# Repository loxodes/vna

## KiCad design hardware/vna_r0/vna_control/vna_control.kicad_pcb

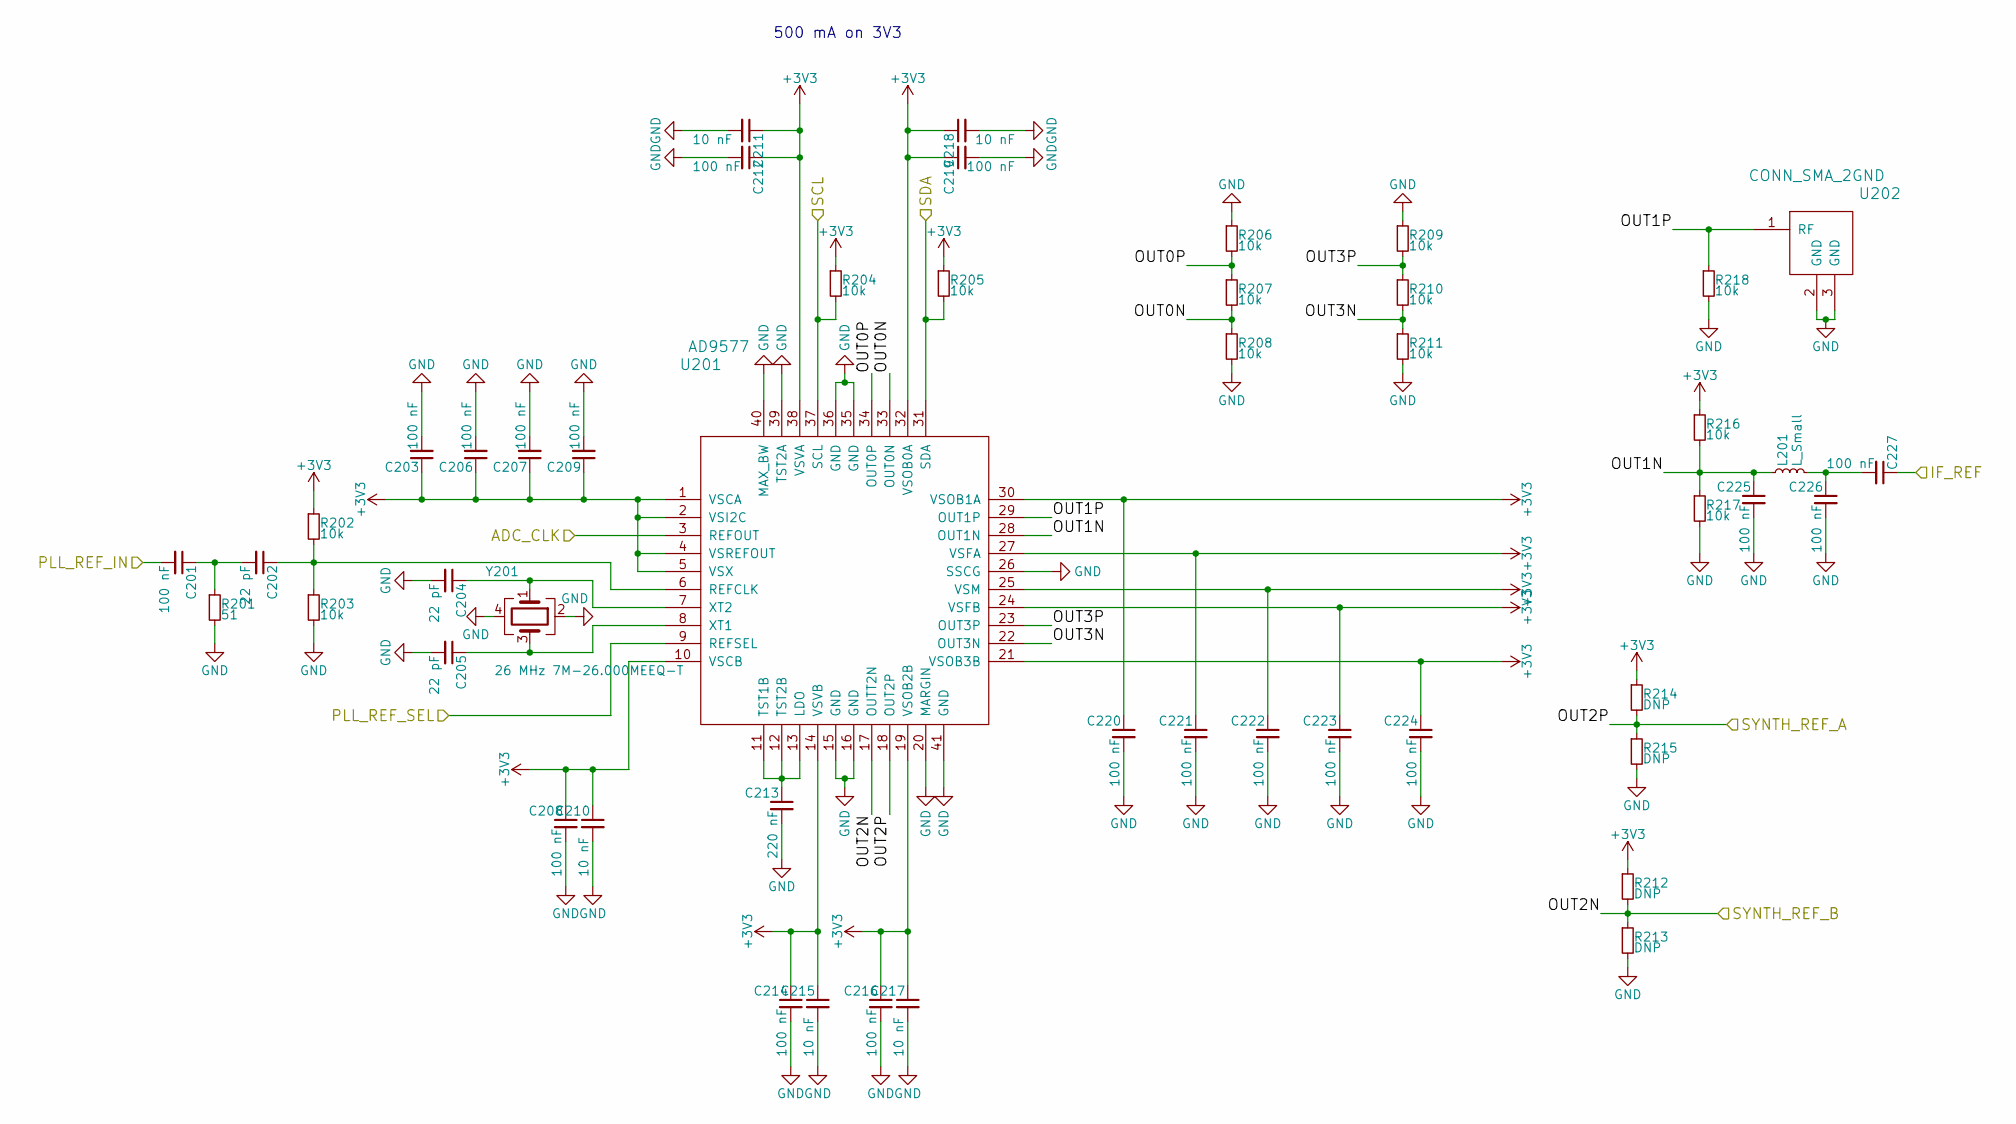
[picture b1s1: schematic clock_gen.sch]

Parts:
C201, C203, C206, C207, C208, C209, C212, C214, C216, C219, C220, C221, C222, C223, C224, C225, C226, C227: 100 nF; C_0402
C202, C204, C205: 22 pF; C_0402
C210, C211, C215, C217, C218: 10 nF; C_0402
C213: 220 nF; C_0402
L201: L_Small; R_0805
R201: 51; R_0402
R202, R203, R204, R205, R206, R207, R208, R209, R210, R211, R216, R217, R218: 10k; R_0402
R212, R213, R214, R215: DNP; R_0402
U201: AD9577; QFN-40-1EP_6x6mm_Pitch0.5mm
U202: CONN_SMA_2GND; 734120110_ufl_umc
Y201: 26 MHz 7M-26.000MEEQ-T; crystal_FA238-TSX3225

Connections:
+3V3: C203.1, C206.1, C207.1, C208.1, C209.1, C210.1, C211.1, C212.1, C214.1, C215.1, C216.1, C217.1, C218.1, C219.1, C220.1, C221.1, C222.1, C223.1, C224.1, R202.1, R204.1, R205.1, R212.1, R214.1, R216.1, U201.1 (VSCA), U201.2 (VSI2C), U201.4 (VSREFOUT), U201.5 (VSX), U201.10 (VSCB), U201.14 (VSVB), U201.19 (VSOB2B), U201.21 (VSOB3B), U201.24 (VSFB), U201.25 (VSM), U201.27 (VSFA), U201.30 (VSOB1A), U201.32 (VSOB0A), U201.38 (VSVA); also elsewhere on the board
/PLL_REF_SEL: U201.9 (REFSEL); also elsewhere on the board
/SCL: R204.2, U201.37 (SCL); also elsewhere on the board
/SDA: R205.2, U201.31 (SDA); also elsewhere on the board
/clock_gen/ADC_CLK: U201.3 (REFOUT); also elsewhere on the board
/clock_gen/IF_REF: C227.1; also elsewhere on the board
/clock_gen/OUT0N: R207.2, R208.1, U201.33 (OUT0N)
/clock_gen/OUT0P: R206.2, R207.1, U201.34 (OUT0P)
/clock_gen/OUT1N: C225.1, L201.1, R216.2, R217.1, U201.28 (OUT1N)
/clock_gen/OUT1P: R218.1, U201.29 (OUT1P), U202.1 (RF)
/clock_gen/OUT3N: R210.2, R211.1, U201.22 (OUT3N)
/clock_gen/OUT3P: R209.2, R210.1, U201.23 (OUT3P)
/clock_gen/PLL_REF_IN: C201.2; also elsewhere on the board
/clock_gen/SYNTH_REF_A: R214.2, R215.1, U201.18 (OUT2P); also elsewhere on the board
/clock_gen/SYNTH_REF_B: R212.2, R213.1, U201.17 (OUTT2N); also elsewhere on the board
GND: C203.2, C204.2, C205.2, C206.2, C207.2, C208.2, C209.2, C210.2, C211.2, C212.2, C213.2, C214.2, C215.2, C216.2, C217.2, C218.2, C219.2, C220.2, C221.2, C222.2, C223.2, C224.2, C225.2, C226.2, R201.2, R203.2, R206.1, R208.2, R209.1, R211.2, R213.2, R215.2, R217.2, R218.2, U201.15 (GND), U201.16 (GND), U201.20 (MARGIN), U201.26 (SSCG), U201.35 (GND), U201.36 (GND), U201.39 (TST2A), U201.40 (MAX_BW), U201.41 (GND), U202.2 (GND), U202.3 (GND), Y201.2, Y201.4; also elsewhere on the board
unnamed: C201.1, C202.2, R201.1
unnamed: C202.1, R202.2, R203.1, U201.6 (REFCLK)
unnamed: C204.1, U201.7 (XT2), Y201.1
unnamed: C205.1, U201.8 (XT1), Y201.3
unnamed: C213.1, U201.11 (TST1B), U201.12 (TST2B), U201.13 (LDO)
unnamed: C226.1, C227.2, L201.2

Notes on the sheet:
500 mA on 3V3

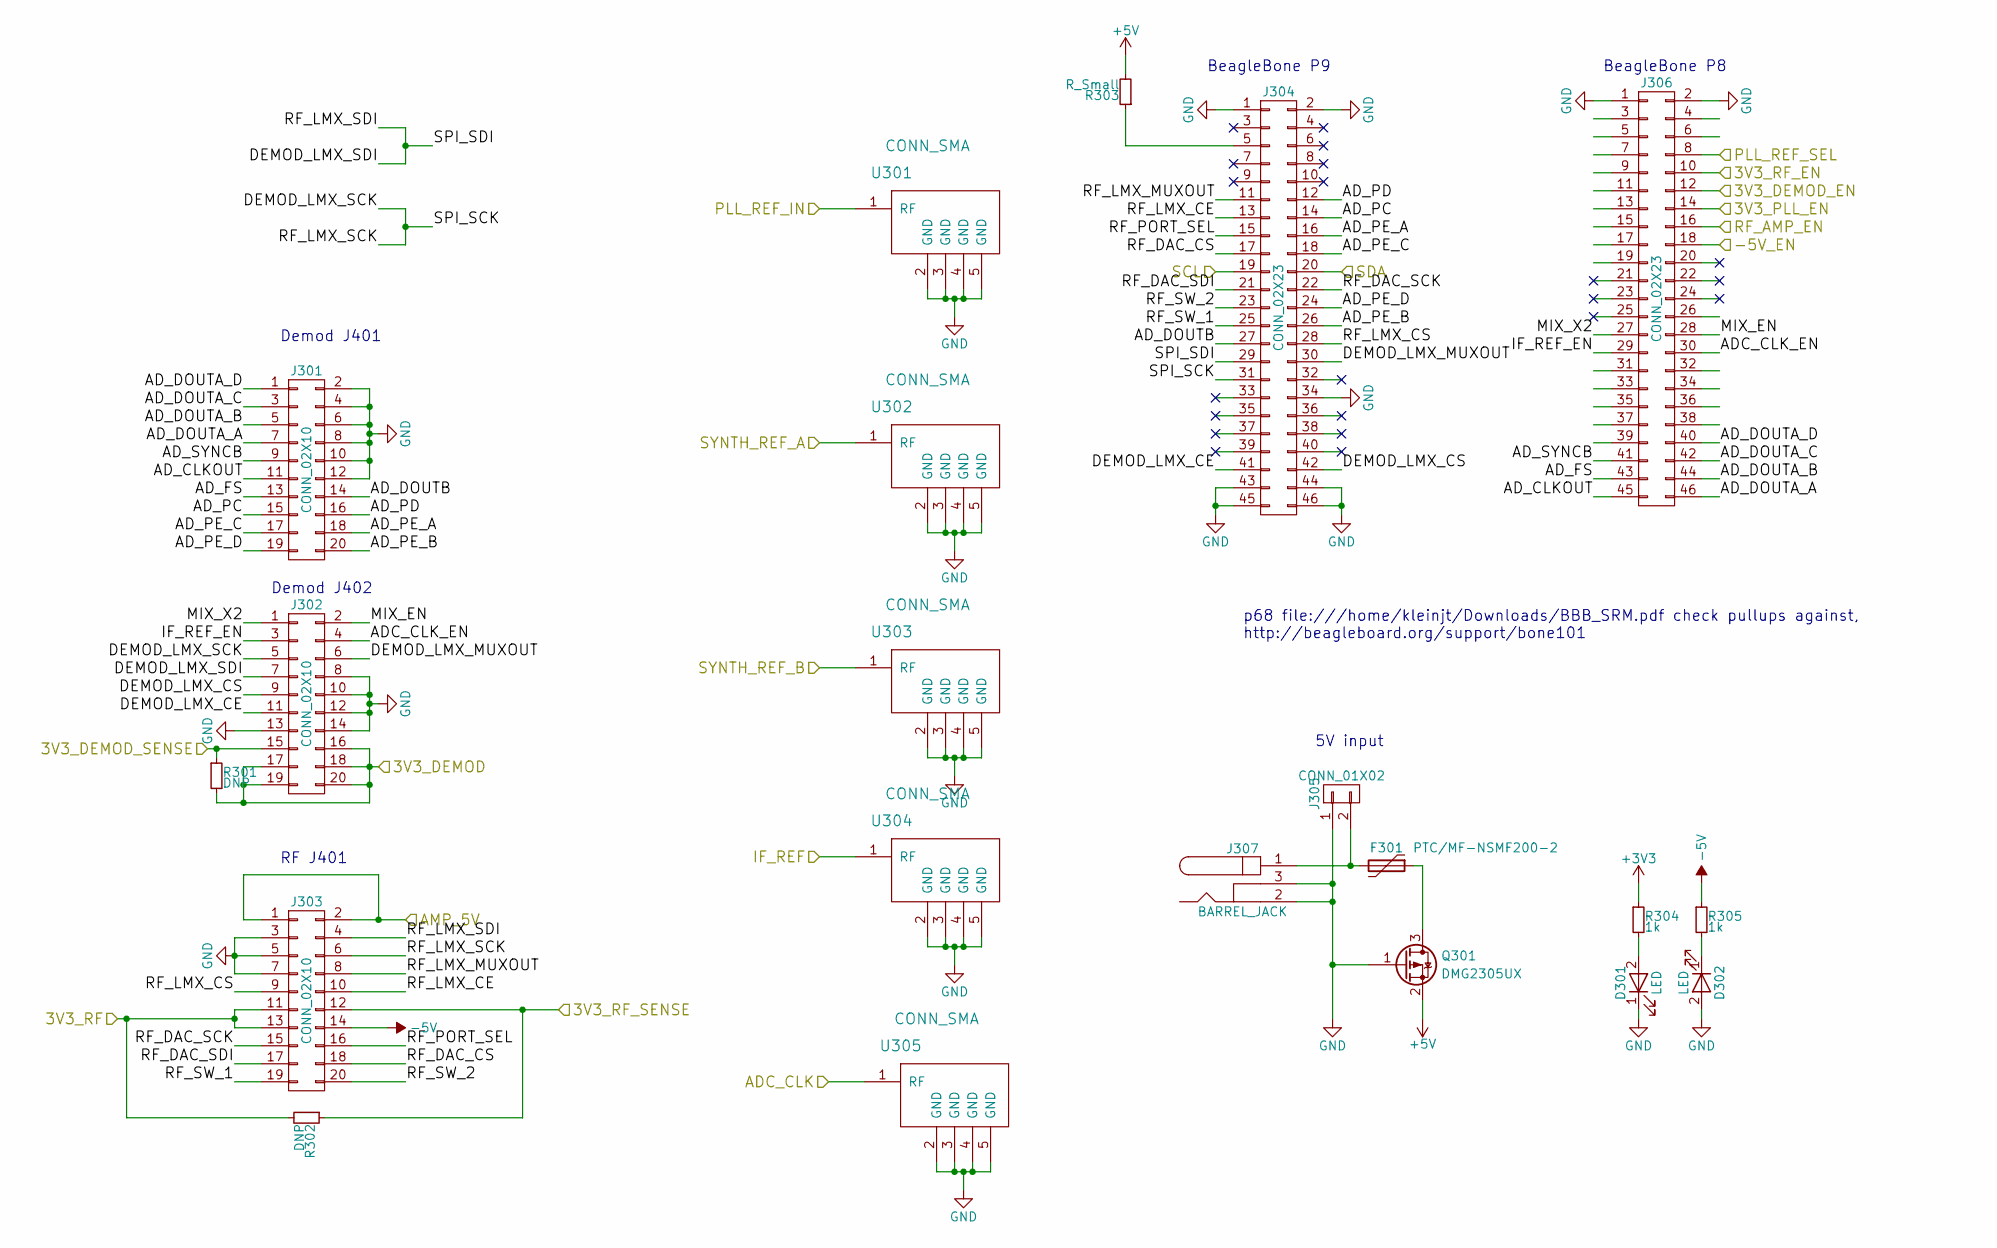
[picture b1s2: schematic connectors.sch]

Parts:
D301, D302: LED; LED_0603
F301: PTC/MF-NSMF200-2; R_1206
J301, J302, J303: CONN_02X10; IDC_Header_Straight_20pins
J304, J306: CONN_02X23; Pin_Header_Straight_2x23
J305: CONN_01X02; TerminalBlock_Pheonix_PT-3.5mm_2pol
J307: BARREL_JACK
Q301: DMG2305UX; SOT-23
R301, R302: DNP; R_0402
R303: R_Small; R_0402
R304, R305: 1k; R_0402
U301, U302, U303, U304, U305: CONN_SMA; 732511150_sma_thin

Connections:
+3V3: R304.1; also elsewhere on the board
+5V: Q301.2 (S), R303.2; also elsewhere on the board
-5V: J303.14, R305.1; also elsewhere on the board
/3V3_DEMOD_EN: J306.12; also elsewhere on the board
/3V3_PLL_EN: J306.14; also elsewhere on the board
/3V3_RF_EN: J306.10; also elsewhere on the board
/-5V_EN: J306.18; also elsewhere on the board
/PLL_REF_SEL: J306.8; also elsewhere on the board
/RF_AMP_EN: J306.16; also elsewhere on the board
/SCL: J304.19; also elsewhere on the board
/SDA: J304.20; also elsewhere on the board
/clock_gen/ADC_CLK: U305.1 (RF); also elsewhere on the board
/clock_gen/IF_REF: U304.1 (RF); also elsewhere on the board
/clock_gen/PLL_REF_IN: U301.1 (RF); also elsewhere on the board
/clock_gen/SYNTH_REF_A: U302.1 (RF); also elsewhere on the board
/clock_gen/SYNTH_REF_B: U303.1 (RF); also elsewhere on the board
/connecors/3V3_DEMOD: J302.16, J302.17, J302.18, J302.19, J302.20, R301.2; also elsewhere on the board
/connecors/3V3_DEMOD_SENSE: J302.15, R301.1; also elsewhere on the board
/connecors/3V3_RF: J303.11, J303.13, R302.2; also elsewhere on the board
/connecors/3V3_RF_SENSE: J303.12, R302.1; also elsewhere on the board
/connecors/ADC_CLK_EN: J302.4, J306.30
/connecors/AD_CLKOUT: J301.11, J306.45
/connecors/AD_DOUTA_A: J301.7, J306.46
/connecors/AD_DOUTA_B: J301.5, J306.44
/connecors/AD_DOUTA_C: J301.3, J306.42
/connecors/AD_DOUTA_D: J301.1, J306.40
/connecors/AD_DOUTB: J301.14, J304.27
/connecors/AD_FS: J301.13, J306.43
/connecors/AD_PC: J301.15, J304.14
/connecors/AD_PD: J301.16, J304.12
/connecors/AD_PE_A: J301.18, J304.16
/connecors/AD_PE_B: J301.20, J304.26
/connecors/AD_PE_C: J301.17, J304.18
/connecors/AD_PE_D: J301.19, J304.24
/connecors/AD_SYNCB: J301.9, J306.41
/connecors/AMP_5V: J303.1, J303.2; also elsewhere on the board
/connecors/DEMOD_LMX_CE: J302.11, J304.41
/connecors/DEMOD_LMX_CS: J302.9, J304.42
/connecors/DEMOD_LMX_MUXOUT: J302.6, J304.30
/connecors/DEMOD_LMX_SCK: J302.5, J303.6, J304.31
/connecors/DEMOD_LMX_SDI: J302.7, J303.4, J304.29
/connecors/IF_REF_EN: J302.3, J306.29
/connecors/MIX_EN: J302.2, J306.28
/connecors/MIX_X2: J302.1, J306.27
/connecors/RF_DAC_CS: J303.18, J304.17
/connecors/RF_DAC_SCK: J303.15, J304.22
/connecors/RF_DAC_SDI: J303.17, J304.21
/connecors/RF_LMX_CE: J303.10, J304.13
/connecors/RF_LMX_CS: J303.9, J304.28
/connecors/RF_LMX_MUXOUT: J303.8, J304.11
/connecors/RF_PORT_SEL: J303.16, J304.15
/connecors/RF_SW_1: J303.19, J304.25
/connecors/RF_SW_2: J303.20, J304.23
GND: D301.1 (K), D302.2 (A), J301.2, J301.4, J301.6, J301.8, J301.10, J301.12, J302.8, J302.10, J302.12, J302.13, J302.14, J303.3, J303.5, J303.7, J304.1, J304.2, J304.34, J304.43, J304.44, J304.45, J304.46, J305.1, J306.1, J306.2, J307.2, J307.3, Q301.1 (G), U301.2 (GND), U301.3 (GND), U301.4 (GND), U301.5 (GND), U302.2 (GND), U302.3 (GND), U302.4 (GND), U302.5 (GND), U303.2 (GND), U303.3 (GND), U303.4 (GND), U303.5 (GND), U304.2 (GND), U304.3 (GND), U304.4 (GND), U304.5 (GND), U305.2 (GND), U305.3 (GND), U305.4 (GND), U305.5 (GND); also elsewhere on the board
unnamed: D301.2 (A), R304.2
unnamed: D302.1 (K), R305.2
unnamed: F301.1, Q301.3 (D)
unnamed: F301.2, J305.2, J307.1
unnamed: J304.5, R303.1

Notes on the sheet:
BeagleBone P9
BeagleBone P8
Demod J401
RF J401
Demod J402
5V input
p68 file:///home/kleinjt/Downloads/BBB_SRM.pdf check pullups against, http://beagleboard.org/support/bone101

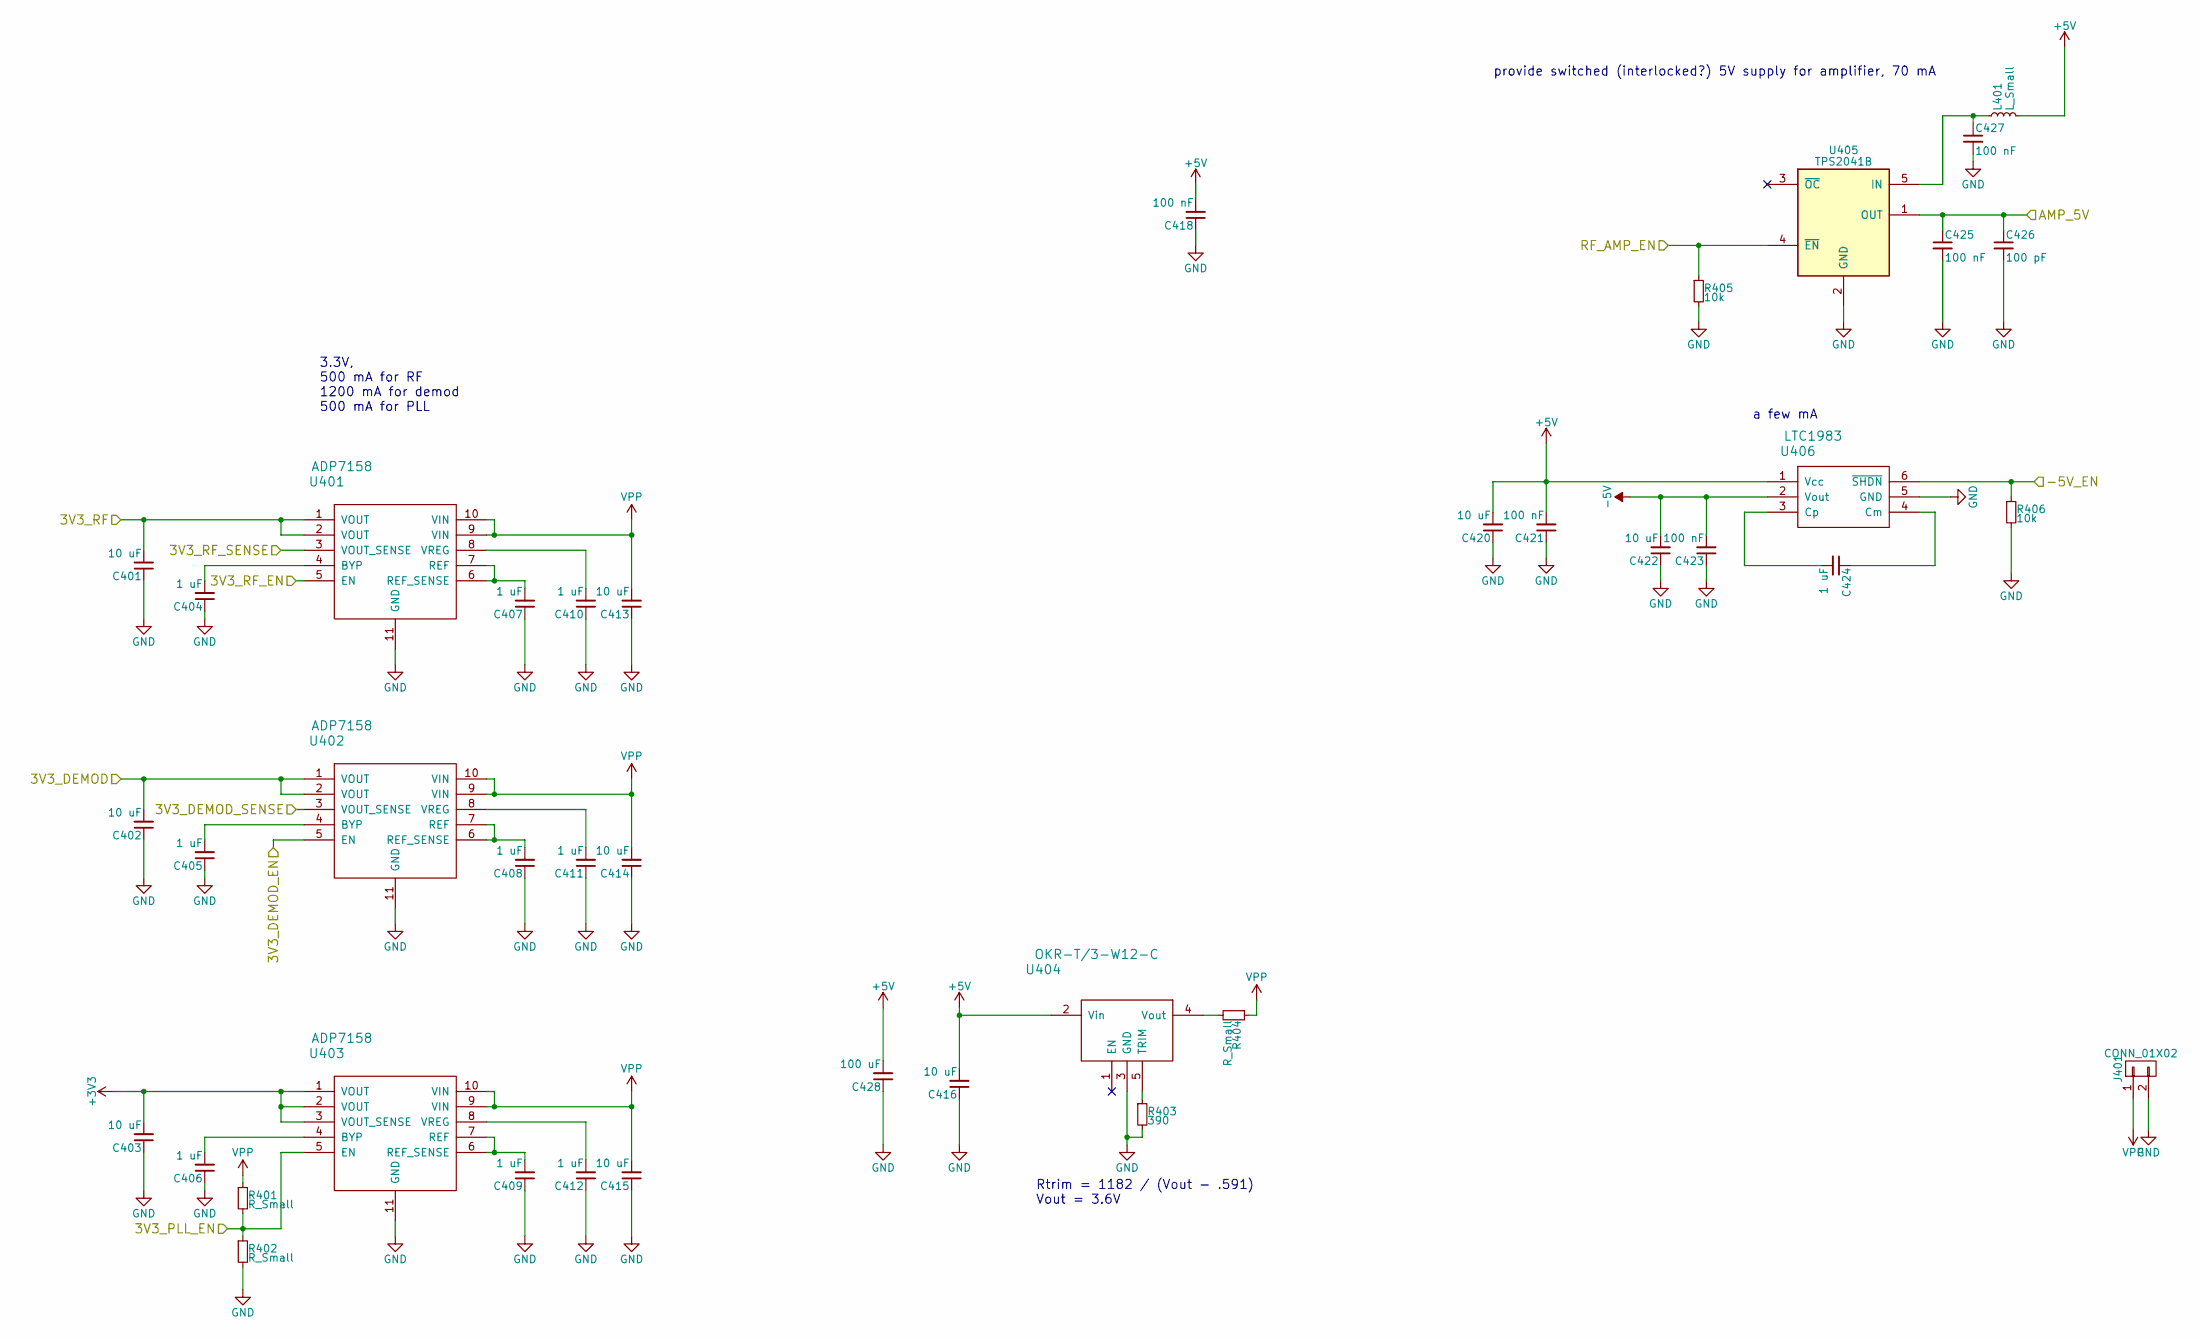
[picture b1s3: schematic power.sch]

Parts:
C401, C402, C403, C413, C414, C415, C416, C420, C422: 10 uF; C_0603
C404, C405, C406, C407, C408, C409, C410, C411, C412, C424: 1 uF; C_0402
C418, C421, C423, C425, C427: 100 nF; C_0402
C426: 100 pF; C_0402
C428: 100 uF; c_elec_10x10
J401: CONN_01X02; TerminalBlock_Pheonix_PT-3.5mm_2pol
L401: L_Small; R_0805
R401, R402: R_Small; R_0402
R403: 390; R_0402
R404: R_Small; R_1206
R405, R406: 10k; R_0402
U401, U402, U403: ADP7158; DFN-10-1EP_3x3mm_Pitch0.5mm
U404: OKR-T/3-W12-C; OKRT3_C72
U405: TPS2041B; SOT-23-5
U406: LTC1983; SOT-23-6

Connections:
+3V3: C403.2, U403.1 (VOUT), U403.2 (VOUT), U403.3 (VOUT_SENSE); also elsewhere on the board
+5V: C416.2, C418.2, C420.2, C421.2, C428.2, L401.2, U404.2 (Vin), U406.1 (Vcc); also elsewhere on the board
-5V: C422.2, C423.2, U406.2 (Vout); also elsewhere on the board
/3V3_DEMOD_EN: U402.5 (EN); also elsewhere on the board
/3V3_PLL_EN: R401.2, R402.1, U403.5 (EN); also elsewhere on the board
/3V3_RF_EN: U401.5 (EN); also elsewhere on the board
/-5V_EN: R406.1, U406.6 (~SHDN); also elsewhere on the board
/RF_AMP_EN: R405.1, U405.4 (~EN); also elsewhere on the board
/connecors/3V3_DEMOD: C402.2, U402.1 (VOUT), U402.2 (VOUT); also elsewhere on the board
/connecors/3V3_DEMOD_SENSE: U402.3 (VOUT_SENSE); also elsewhere on the board
/connecors/3V3_RF: C401.2, U401.1 (VOUT), U401.2 (VOUT); also elsewhere on the board
/connecors/3V3_RF_SENSE: U401.3 (VOUT_SENSE); also elsewhere on the board
/connecors/AMP_5V: C425.1, C426.1, U405.1 (OUT); also elsewhere on the board
GND: C401.1, C402.1, C403.1, C404.1, C405.1, C406.1, C407.1, C408.1, C409.1, C410.1, C411.1, C412.1, C413.1, C414.1, C415.1, C416.1, C418.1, C420.1, C421.1, C422.1, C423.1, C425.2, C426.2, C427.2, C428.1, J401.2, R402.2, R403.2, R405.2, R406.2, U401.11 (GND), U402.11 (GND), U403.11 (GND), U404.3 (GND), U405.2 (GND), U406.5 (GND); also elsewhere on the board
unnamed: C404.2, U401.4 (BYP)
unnamed: C405.2, U402.4 (BYP)
unnamed: C406.2, U403.4 (BYP)
unnamed: C407.2, U401.6 (REF_SENSE), U401.7 (REF)
unnamed: C408.2, U402.6 (REF_SENSE), U402.7 (REF)
unnamed: C409.2, U403.6 (REF_SENSE), U403.7 (REF)
unnamed: C410.2, U401.8 (VREG)
unnamed: C411.2, U402.8 (VREG)
unnamed: C412.2, U403.8 (VREG)
unnamed: C424.1, U406.4 (Cm)
unnamed: C424.2, U406.3 (Cp)
unnamed: C427.1, L401.1, U405.5 (IN)
unnamed: R403.1, U404.5 (TRIM)
unnamed: R404.2, U404.4 (Vout)
VPP: C413.2, C414.2, C415.2, J401.1, R401.1, R404.1, U401.9 (VIN), U401.10 (VIN), U402.9 (VIN), U402.10 (VIN), U403.9 (VIN), U403.10 (VIN)

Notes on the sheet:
provide switched (interlocked?) 5V supply for amplifier, 70 mA
a few mA
3.3V, 500 mA for RF 1200 mA for demod 500 mA for PLL
Rtrim = 1182 / (Vout - .591) Vout = 3.6V

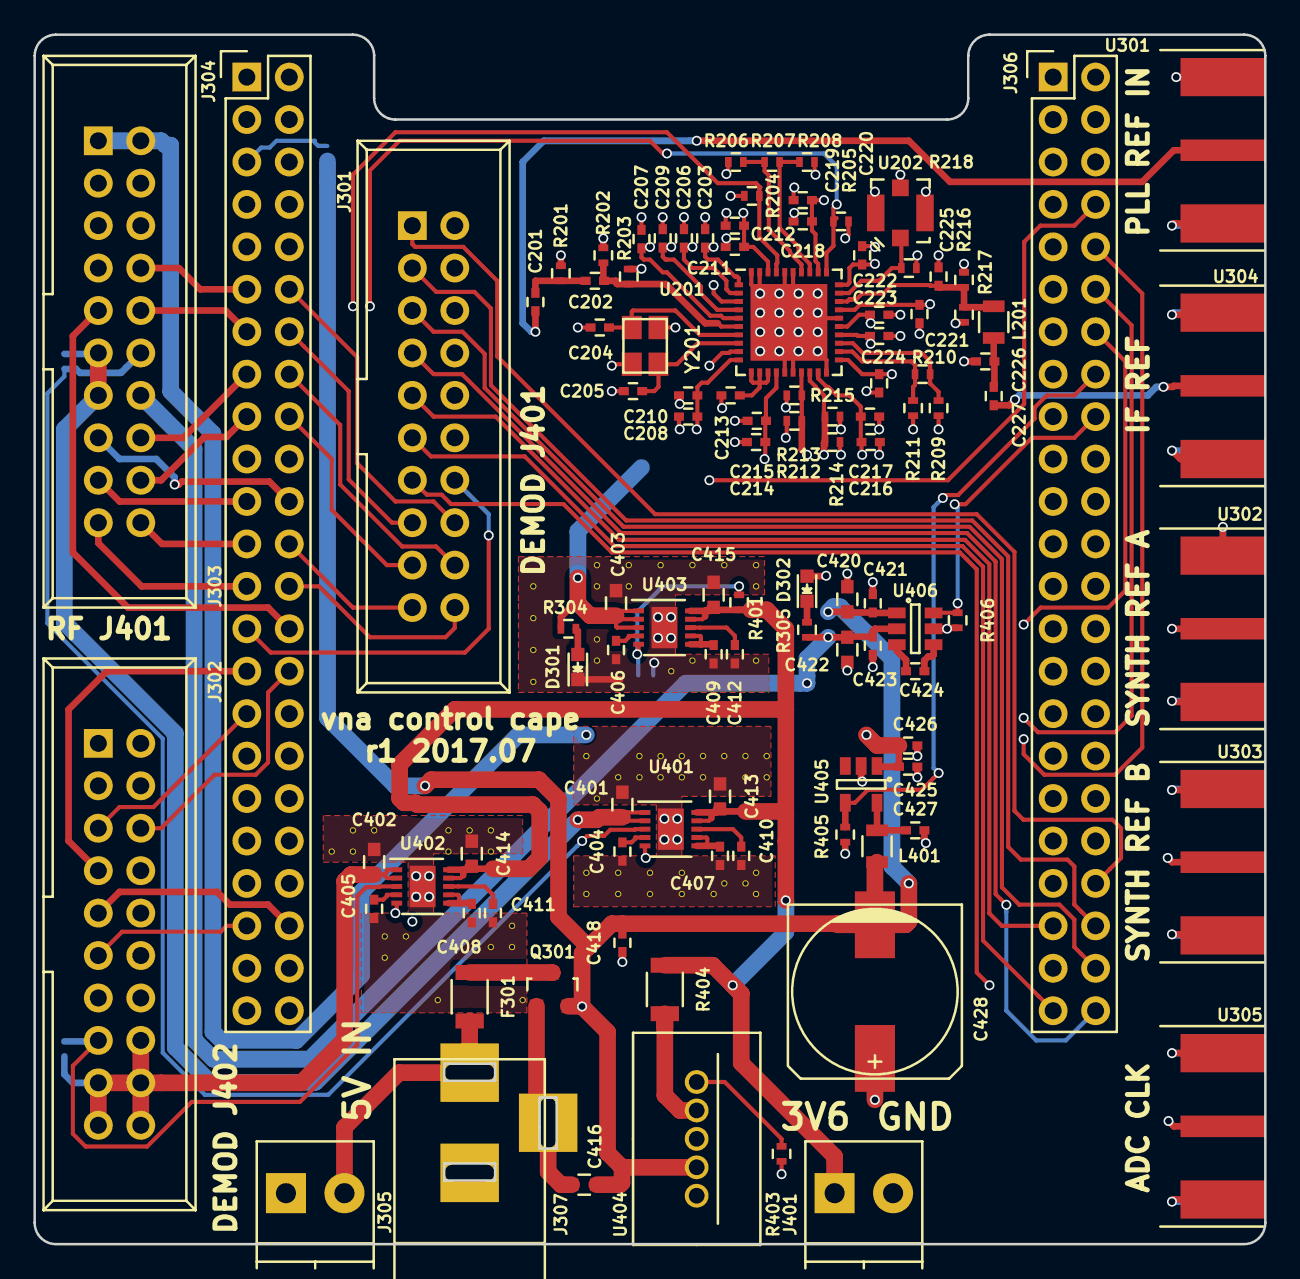
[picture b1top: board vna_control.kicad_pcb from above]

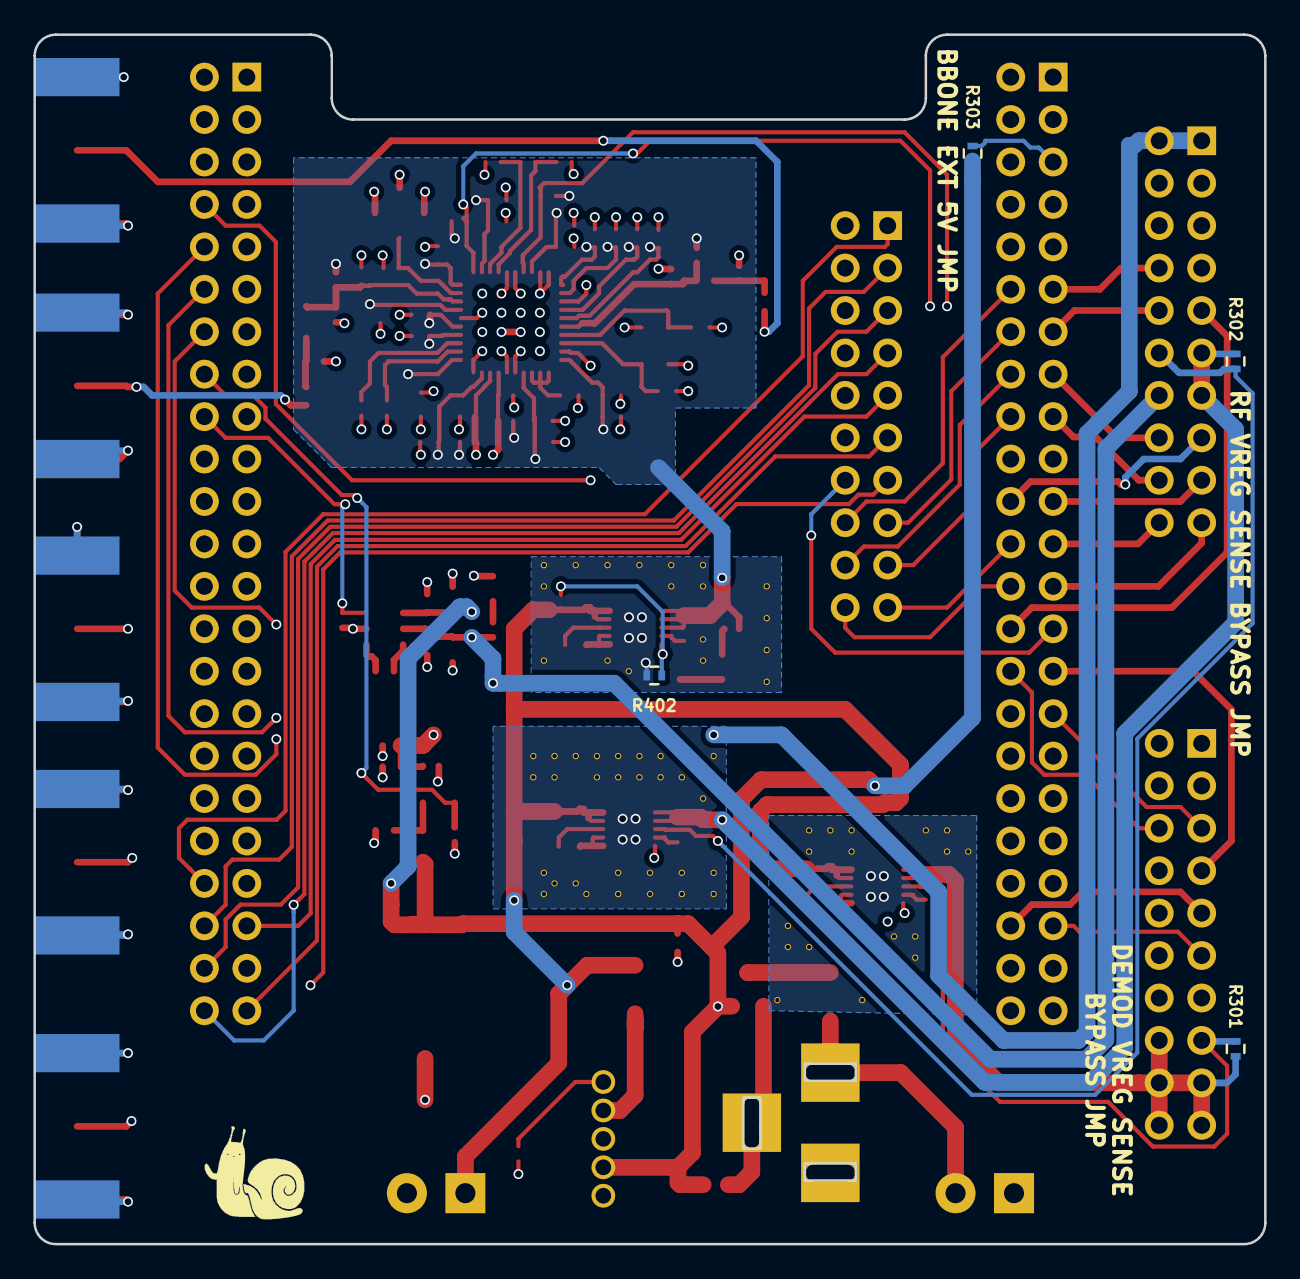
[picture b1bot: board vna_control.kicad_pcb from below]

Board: 4 copper layers, 73.7 x 72.4 mm, 110 parts (4 on the bottom side), 86 nets.

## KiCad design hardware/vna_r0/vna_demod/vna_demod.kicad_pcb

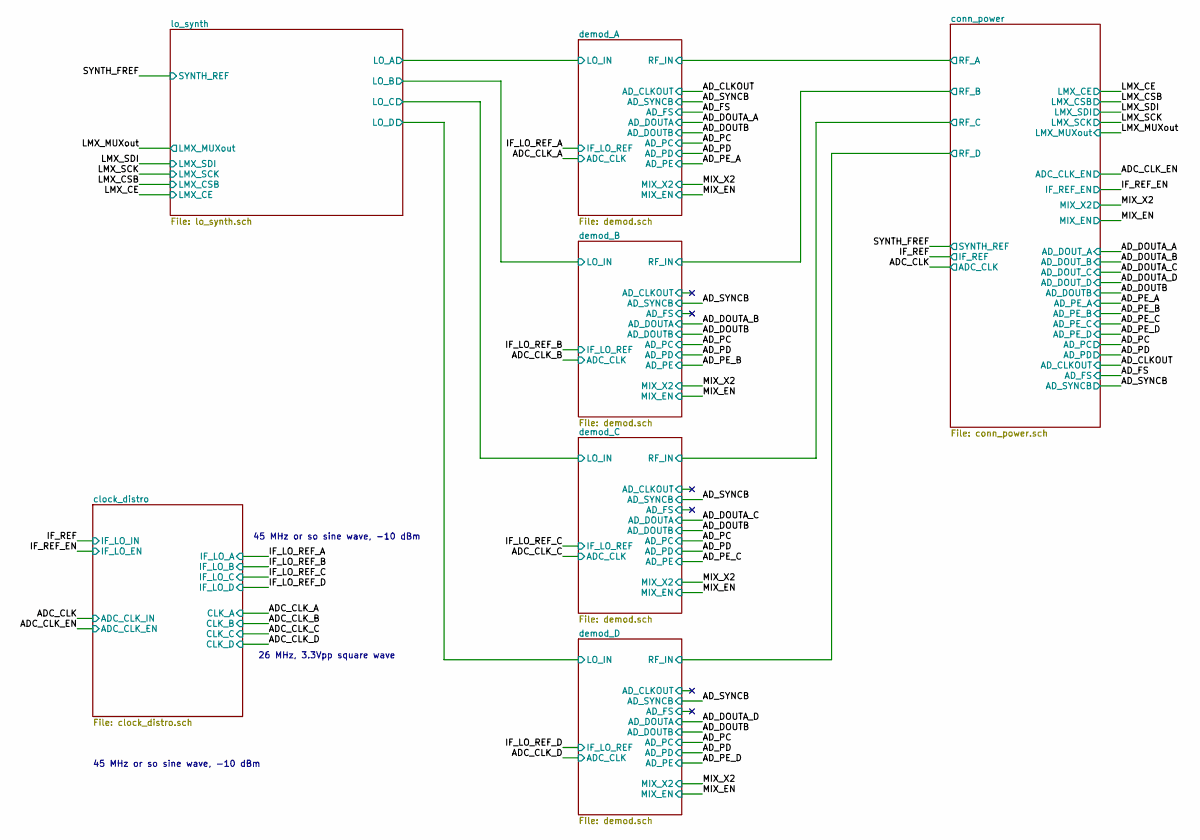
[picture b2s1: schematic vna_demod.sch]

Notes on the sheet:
26 MHz, 3.3Vpp square wave
45 MHz or so sine wave, -10 dBm

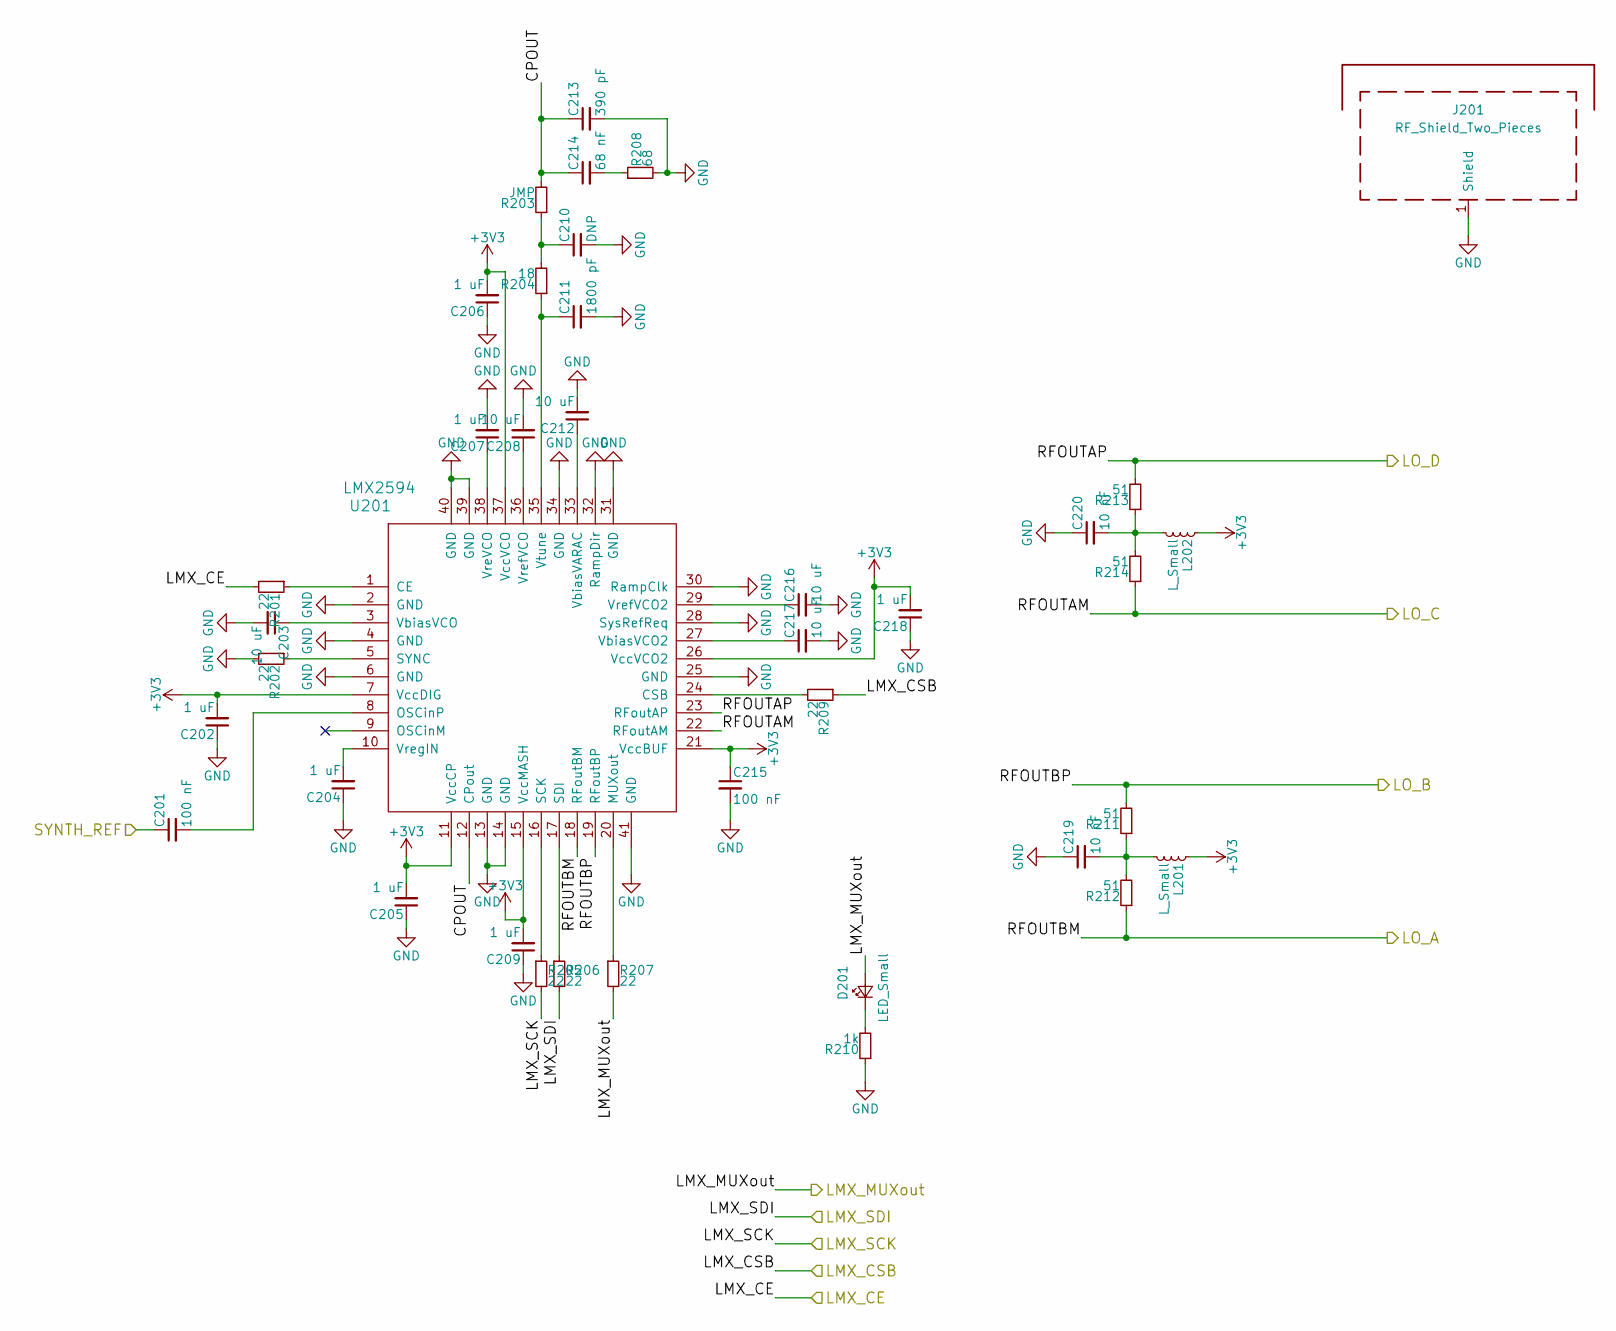
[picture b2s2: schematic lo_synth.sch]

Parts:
C201, C215: 100 nF; C_0402
C202, C204, C205, C206, C207, C209, C218: 1 uF; C_0402
C203, C208, C212, C216, C217: 10 uF; C_0603
C210: DNP; C_0402
C211: 1800 pF; C_0402
C213: 390 pF; C_0402
C214: 68 nF; C_0402
C219, C220: 10 nF; C_0402
D201: LED_Small; LED_0603
J201: RF_Shield_Two_Pieces; Laird_Technologies_BMI-S-209-F_29.36x18.50mm
L201, L202: L_Small; R_0402
R201, R202, R205, R206, R207, R209: 22; R_0402
R203: JMP; R_0402
R204: 18; R_0402
R208: 68; R_0402
R210: 1k; R_0402
R211, R212, R213, R214: 51; R_0402
U201: LMX2594; QFN-40-1EP_6x6mm_Pitch0.5mm

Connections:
+3V3: C202.2, C205.2, C206.2, C209.2, C215.1, C218.2, L201.1, L202.1, U201.7 (VccDIG), U201.11 (VccCP), U201.15 (VccMASH), U201.21 (VccBUF), U201.26 (VccVCO2), U201.37 (VccVCO); also elsewhere on the board
/LMX_CE: R201.2; also elsewhere on the board
/LMX_CSB: R209.1; also elsewhere on the board
/LMX_MUXout: D201.2 (A), R207.2; also elsewhere on the board
/LMX_SCK: R205.2; also elsewhere on the board
/LMX_SDI: R206.2; also elsewhere on the board
/SYNTH_FREF: C201.1; also elsewhere on the board
/lo_synth/CPOUT: C213.1, C214.1, R203.2, U201.12 (CPout)
/lo_synth/LO_A: R212.1, U201.18 (RFoutBM); also elsewhere on the board
/lo_synth/LO_B: R211.2, U201.19 (RFoutBP); also elsewhere on the board
/lo_synth/LO_C: R214.1, U201.22 (RFoutAM); also elsewhere on the board
/lo_synth/LO_D: R213.2, U201.23 (RFoutAP); also elsewhere on the board
GND: C202.1, C203.2, C204.1, C205.1, C206.1, C207.2, C208.2, C209.1, C210.2, C211.2, C212.2, C213.2, C215.2, C216.2, C217.2, C218.1, C219.1, C220.1, J201.1, R202.2, R208.2, R210.1, U201.2 (GND), U201.4 (GND), U201.6 (GND), U201.13 (GND), U201.14 (GND), U201.25 (GND), U201.28 (SysRefReq), U201.30 (RampClk), U201.31 (GND), U201.32 (RampDir), U201.34 (GND), U201.39 (GND), U201.40 (GND), U201.41 (GND); also elsewhere on the board
unnamed: C201.2, U201.8 (OSCinP)
unnamed: C203.1, U201.3 (VbiasVCO)
unnamed: C204.2, U201.10 (VregIN)
unnamed: C207.1, U201.38 (VreVCO)
unnamed: C208.1, U201.36 (VrefVCO)
unnamed: C210.1, R203.1, R204.2
unnamed: C211.1, R204.1, U201.35 (Vtune)
unnamed: C212.1, U201.33 (VbiasVARAC)
unnamed: C214.2, R208.1
unnamed: C216.1, U201.29 (VrefVCO2)
unnamed: C217.1, U201.27 (VbiasVCO2)
unnamed: C219.2, L201.2, R211.1, R212.2
unnamed: C220.2, L202.2, R213.1, R214.2
unnamed: D201.1 (K), R210.2
unnamed: R201.1, U201.1 (CE)
unnamed: R202.1, U201.5 (SYNC)
unnamed: R205.1, U201.16 (SCK)
unnamed: R206.1, U201.17 (SDI)
unnamed: R207.1, U201.20 (MUXout)
unnamed: R209.2, U201.24 (CSB)

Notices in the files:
parts and their libraries:
Copyright 2016 Accelerated Designs. All rights reserved.
